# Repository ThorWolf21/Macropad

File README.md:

# TWPad

TWPad is a 7 key 2 Rotary encoder macropad. It has per key leds(Not under the rotary encoders) + 4 status/ambient leds, using SK6812MINI-E leds

It is an entry to the hackpad program

---

## Features

- 3D printed case
- 2 EC11 Rotary encoders for volume and others
- 11 SK6812MINI-E leds. 7 for per key lighting and 4 for status/ambient lighting
- 7 keys

---

## CAD Model

Here is some pictures of the parts and the testfit

Top-plate:

Bottom/case:

Testfit:

---

## PCB

Here is the pcb i designed for my macropad

Schematic:

PCB:

---

## Firmware

KMK

3 layers 7 Btns 1 RotEnc per layer 
one rotary encoder is used for layerswitching

I have not finalized the macros because i dont know what i want

---

## BOM

I am pretty sure this is everything:

- 7x Cherry MX Switches
- 7x DSA keycaps
- 9x Through-hole 1N4148 Diodes
- 11x SK6812 MINI-E LEDs
- 2x EC11 Rotary Encoders
- 1x Seeed XIAO RP2040
- 1x Case (x printed parts)
- 4x M3x16mm screws
- 4x M3x5mx4mm heatset inserts

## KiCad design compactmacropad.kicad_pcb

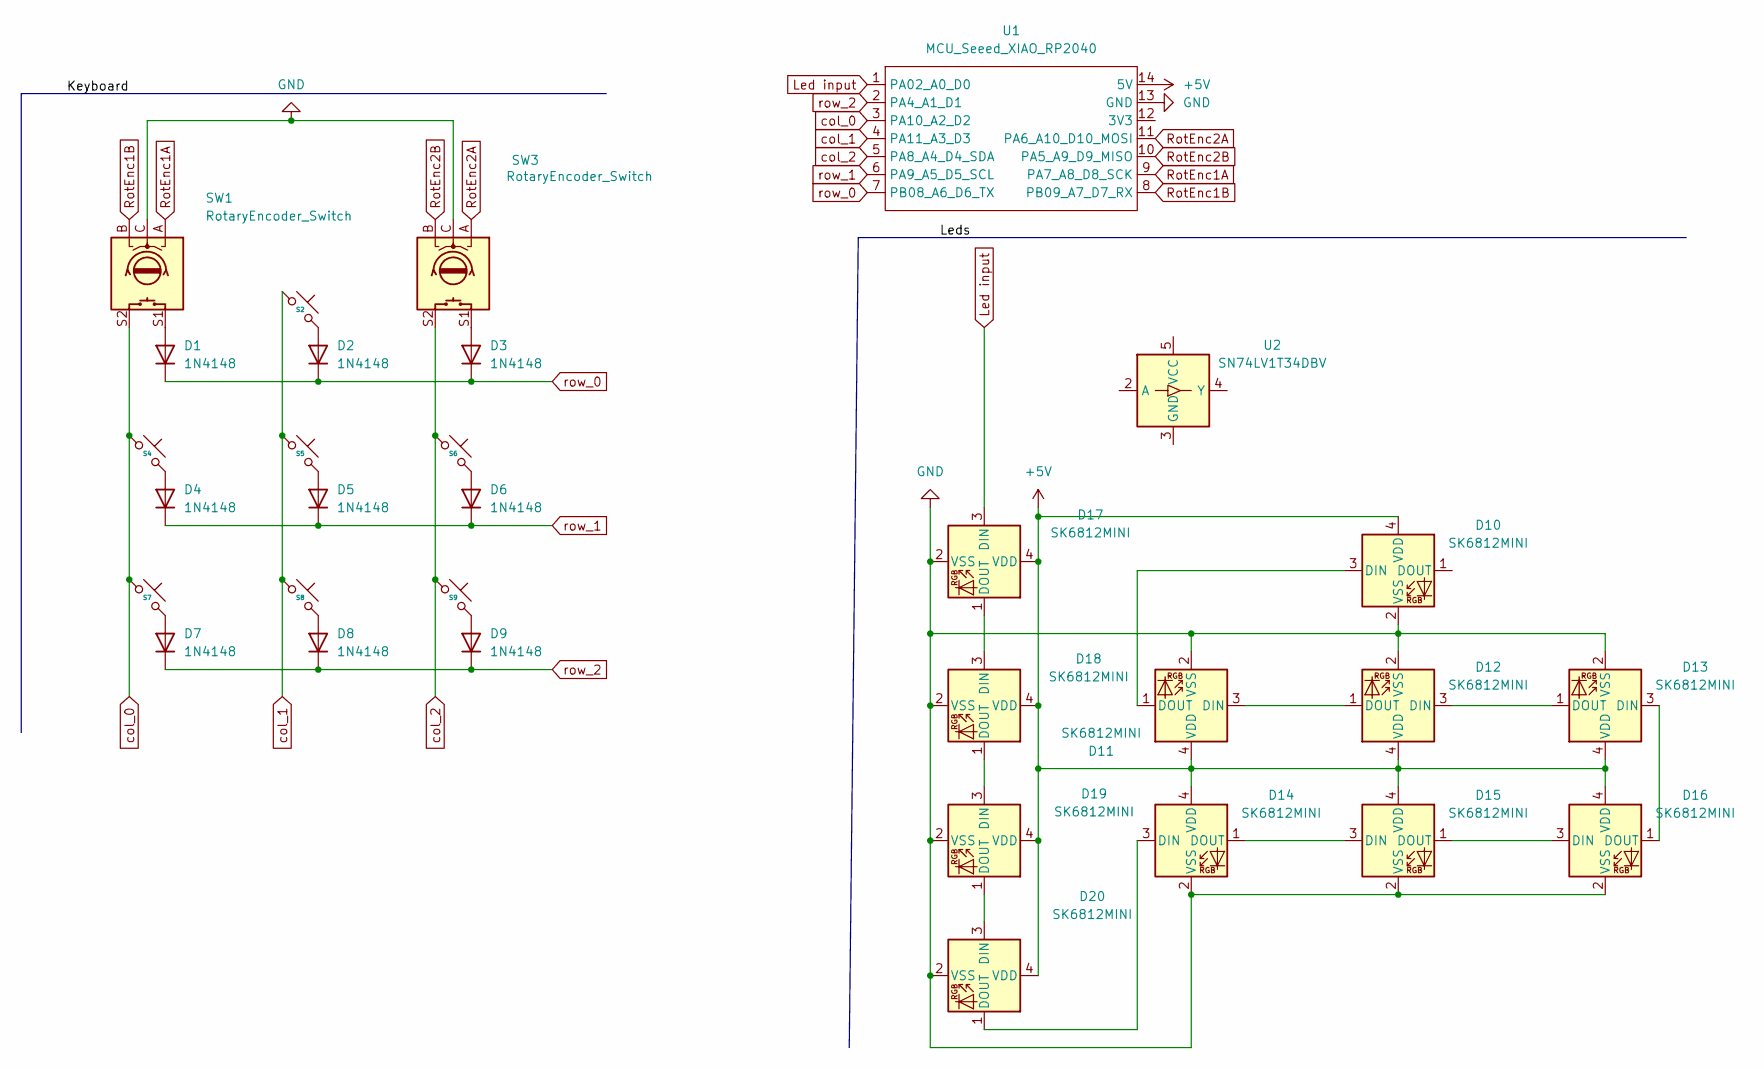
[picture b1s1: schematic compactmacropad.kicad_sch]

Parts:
D1, D2, D3, D4, D5, D6, D7, D8, D9: 1N4148; D_DO-35_SOD27_P7.62mm_Horizontal
D10, D11, D12, D13, D14, D15, D16, D17, D18, D19, D20: SK6812MINI; LED_SK6812MINI_PLCC4_3.5x3.5mm_P1.75mm
S2, S4, S5, S6, S7, S8, S9: SW_Cherry_MX_1.00u_PCB
SW1, SW3: RotaryEncoder_Switch; RotaryEncoder_Alps_EC11E-Switch_Vertical_H20mm
U1: MCU_Seeed_XIAO_RP2040; XIAO-MG24-DIP
U2: SN74LV1T34DBV; SOT-23-5

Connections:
+5V: D10.4 (VDD), D11.4 (VDD), D12.4 (VDD), D13.4 (VDD), D14.4 (VDD), D15.4 (VDD), D16.4 (VDD), D17.4 (VDD), D18.4 (VDD), D19.4 (VDD), D20.4 (VDD), U1.14 (5V)
GND: D10.2 (VSS), D11.2 (VSS), D12.2 (VSS), D13.2 (VSS), D14.2 (VSS), D15.2 (VSS), D16.2 (VSS), D17.2 (VSS), D18.2 (VSS), D19.2 (VSS), D20.2 (VSS), SW1.C, SW3.C, U1.13 (GND)
Led input: D17.3 (DIN), U1.1 (PA02_A0_D0)
unnamed: D1.2 (A), SW1.S1
unnamed: D2.2 (A), S2.2
unnamed: D3.2 (A), SW3.S1
unnamed: D4.2 (A), S4.2
unnamed: D5.2 (A), S5.2
unnamed: D6.2 (A), S6.2
unnamed: D7.2 (A), S7.2
unnamed: D8.2 (A), S8.2
unnamed: D9.2 (A), S9.2
unnamed: D10.3 (DIN), D11.1 (DOUT)
unnamed: D11.3 (DIN), D12.1 (DOUT)
unnamed: D12.3 (DIN), D13.1 (DOUT)
unnamed: D13.3 (DIN), D16.1 (DOUT)
unnamed: D14.3 (DIN), D20.1 (DOUT)
unnamed: D14.1 (DOUT), D15.3 (DIN)
unnamed: D15.1 (DOUT), D16.3 (DIN)
unnamed: D17.1 (DOUT), D18.3 (DIN)
unnamed: D18.1 (DOUT), D19.3 (DIN)
unnamed: D19.1 (DOUT), D20.3 (DIN)
RotEnc1A: SW1.A, U1.9 (PA7_A8_D8_SCK)
RotEnc1B: SW1.B, U1.8 (PB09_A7_D7_RX)
RotEnc2A: SW3.A, U1.11 (PA6_A10_D10_MOSI)
RotEnc2B: SW3.B, U1.10 (PA5_A9_D9_MISO)
col_0: S4.1, S7.1, SW1.S2, U1.3 (PA10_A2_D2)
col_1: S2.1, S5.1, S8.1, U1.4 (PA11_A3_D3)
col_2: S6.1, S9.1, SW3.S2, U1.5 (PA8_A4_D4_SDA)
row_0: D1.1 (K), D2.1 (K), D3.1 (K), U1.7 (PB08_A6_D6_TX)
row_1: D4.1 (K), D5.1 (K), D6.1 (K), U1.6 (PA9_A5_D5_SCL)
row_2: D7.1 (K), D8.1 (K), D9.1 (K), U1.2 (PA4_A1_D1)

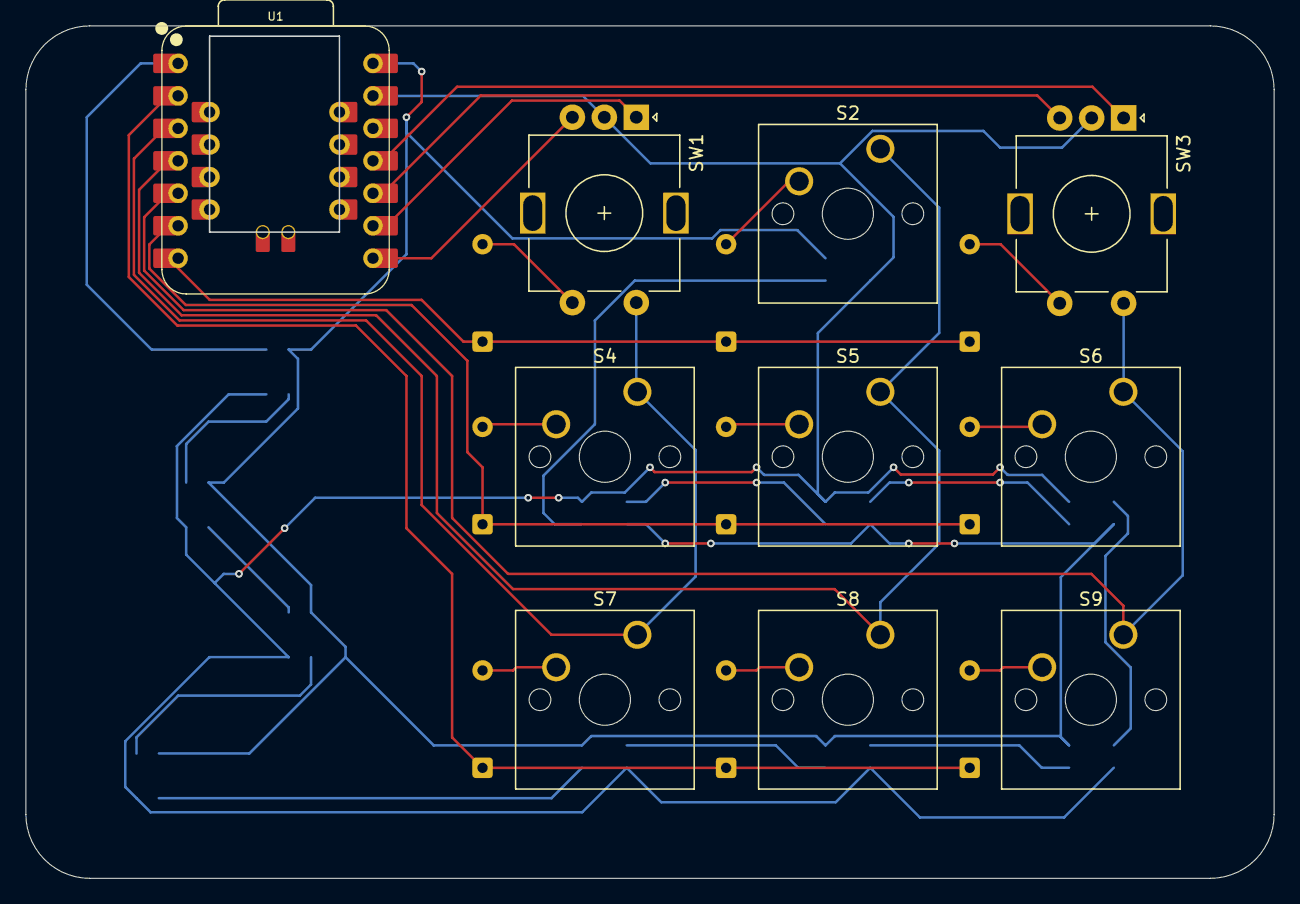
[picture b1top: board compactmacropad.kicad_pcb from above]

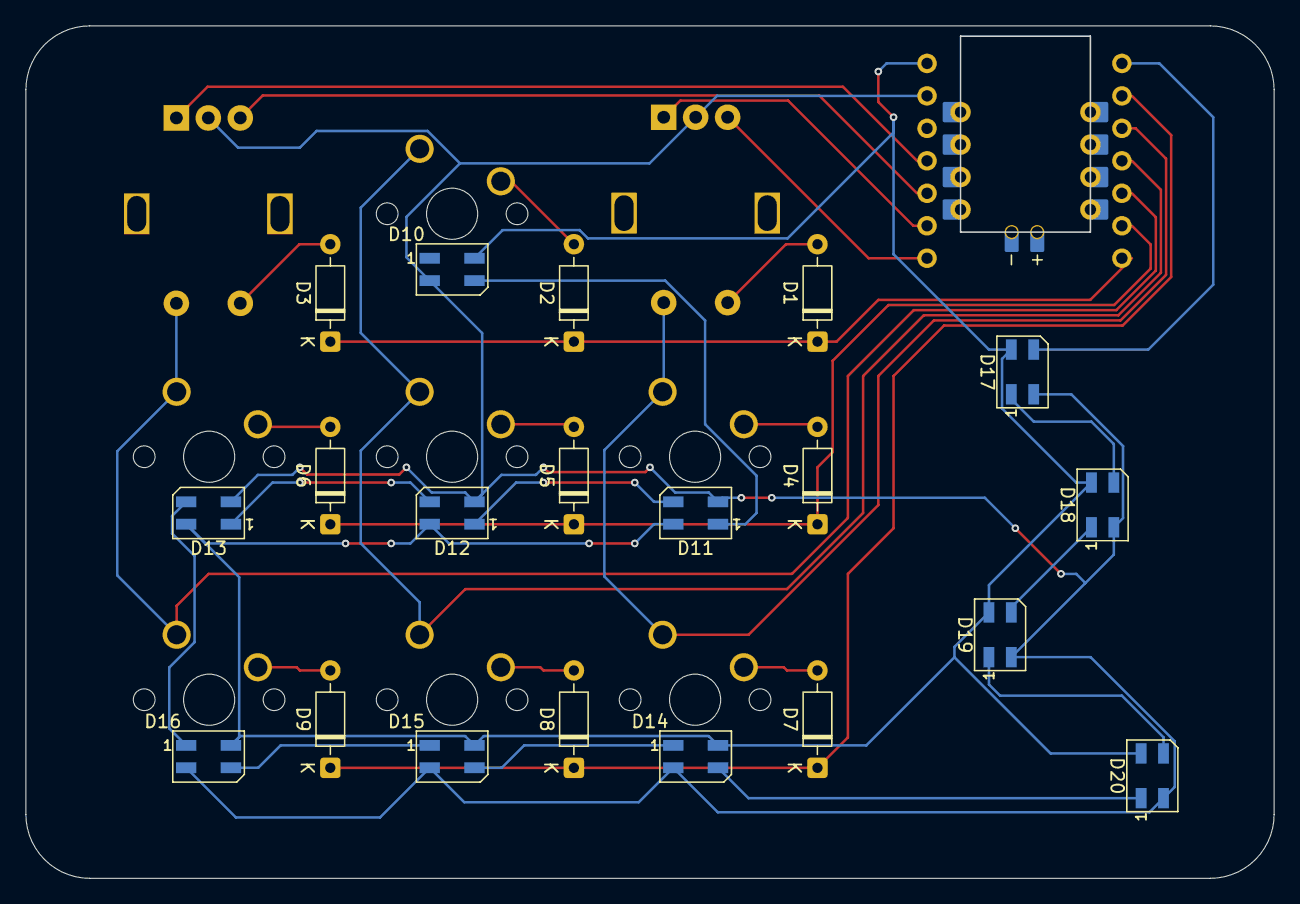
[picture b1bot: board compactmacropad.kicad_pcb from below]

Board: 2 copper layers, 97.6 x 66.6 mm, 30 parts (20 on the bottom side), 32 nets.

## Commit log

2025-12-11 Organizing into folders
2025-12-11 more organizing
2025-12-11 my bad
2025-12-11 Adding imgs
2025-12-11 BOM update
2025-12-11 progress update
2025-12-12 readme update
2025-12-12 maybe?
2025-12-13 fixed cad
2025-12-14 fix typo in README
2025-12-14 firmwae
2025-12-14 Added the rotary encoders
2025-12-14 added layers n stuff
2025-12-14 readme firmware update
2025-12-14 Update case description in README
2025-12-14 Adding necesary files/updating them for cad and pcb
2025-12-20 Firmware update and configuring
2025-12-25 Add MIT License to the project
2025-12-25 Rename LICENSE to LICENSE.txt
